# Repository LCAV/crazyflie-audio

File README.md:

# Audio processing for Crazyflie drone

This repository contains the hardware files, firmware and other documentation for the audio deck of the Crazyflie drone. 

## Overview

This repository is part of the experimental framework described in the [paper](https://doi.org/10.1109/LRA.2022.3194669):
```
F. Dümbgen, A. Hoffet, M. Kolundžija, A. Scholefield, and M. Vetterli, "Blind as a bat: audible 
echolocation on small robots", IEEE Robotics and Automation Letters (Early Access), 2022.
```

The framework includes all components listed below. The components are kept modular so that researchers may focus only on what's relevant to them. For instance, to recreate the audio extension deck and perform more research on audio-based navigation on drones, only repository 2. is necessary; to run the audio-based algorithms in ROS but for a different robot, only repository 1. is enough as a starting point.      

1. [ROS processing pipeline](https://github.com/LCAV/audioROS) for processing audio for tasks such as obstacle detection and sound source localization. 
2. [Audio deck firmware](https://github.com/LCAV/crazyflie-audio) (**this repository**), which also includes the PCB files for reproducing the audio deck. 
3. [Public datasets](https://github.com/LCAV/audio-localization-dataset), for audio-based localization on the e-puck2 robot and the Crazyflie drone. 
4. [Crazyflie firmware](https://github.com/LCAV/crazyflie-firmware) (fork from official vendor firmware), with an added [audio deck driver](https://github.com/LCAV/crazyflie-firmware/blob/master/src/deck/drivers/src/audio_deck.c).
5. [Gtsam extension](https://github.com/duembgen/gtsam) for performing factor-graph inference using the echolocation measurements. 

## Contents

- `firmware/`: Firmware to run on the audio shield, which extracts and transmits microphone data to the Crazyflie PCB. 
- `hardware/`: *KiCad* PCB design files for audio shield.
- `python/`: Helper functions to generate hard-coded sweeps etc. 
- `flight_control/`: Simple scripts to fly the Crazyflie drone for testing.
- `doc/`: Some documentation and helpers.

## Audio deck driver

The driver of the audio deck, running on the Crazyflie, is available in [this fork](https://github.com/lcav/crazyflie-firmware) of the official firmware.

## Contributors 

In alphabetical order:

- Isaac Bernardino Dinis 
- Frederike Dümbgen
- Adrien Hoffet

## License

All material in this repo is provided with the MIT license.

## EEPROM

Parameters to set in `crazyflie-lib-python/examples/write_ow.py`: 

```
mems[0].vid = 0xBC
mems[0].pid = 0xFF
board_name_id = OWElement.element_mapping[1]
board_rev_id = OWElement.element_mapping[2]
mems[0].elements[board_name_id] = 'Audio Shield'
mems[0].elements[board_rev_id] = 'V2'
```

## References

Please refer to the below publications for more information. 

[1] [RA-L paper](https://doi.org/10.1109/LRA.2022.3194669) (main reference)
```
F. Dümbgen, A. Hoffet, M. Kolundžija, A. Scholefield, and M. Vetterli, "Blind as a bat: audible 
echolocation on small robots", IEEE Robotics and Automation Letters (Early Access), 2022. 
```

[2] [Ph.D. dissertation](https://infoscience.epfl.ch/record/290057) (including additional methods and experimental analysis):  
```
F. Dümbgen, "Blind as a bat: spatial perception without sight", Ph.D. disseration, 
École Polytechnique Fédérale de Lausanne, 2021.
```

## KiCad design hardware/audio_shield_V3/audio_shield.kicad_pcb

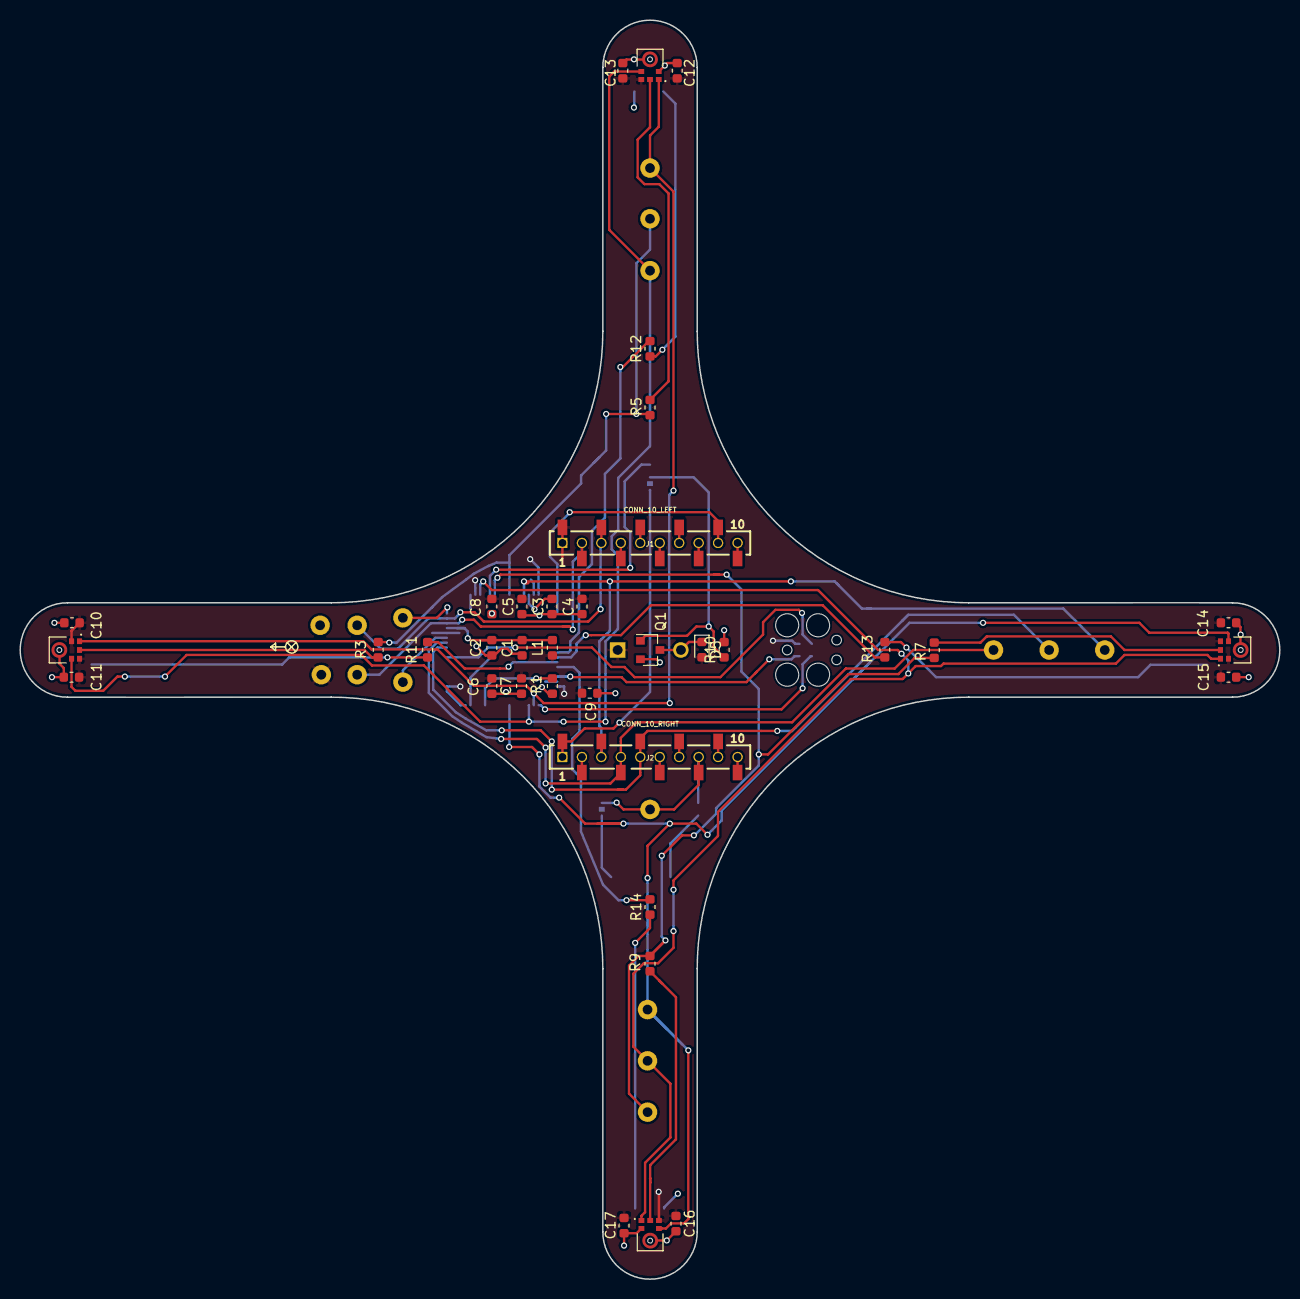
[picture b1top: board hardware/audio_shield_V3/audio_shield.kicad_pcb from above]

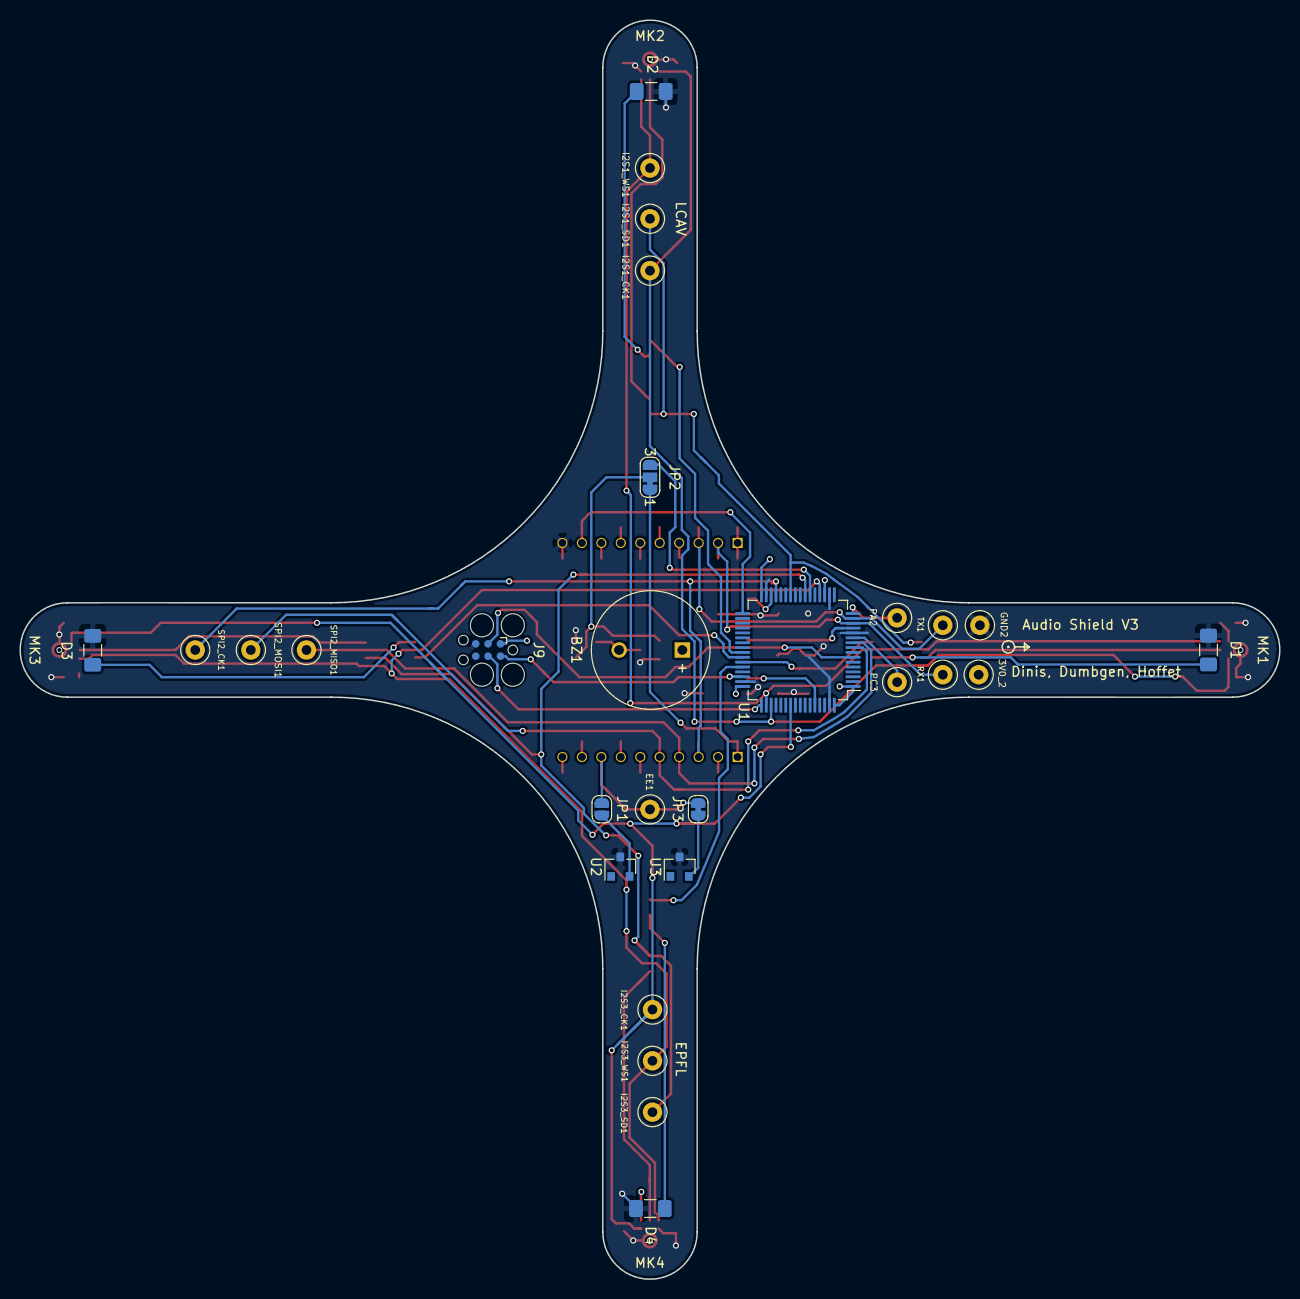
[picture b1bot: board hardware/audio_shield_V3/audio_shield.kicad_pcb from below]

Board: 2 copper layers, 129.5 x 129.4 mm, 64 parts (28 on the bottom side), 41 nets.

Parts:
3V0_2: TestPoint; TestPoint_Loop_D2.50mm_Drill1.0mm_LowProfile
BZ1: KXG1201B; MagneticBuzzer_ProSignal_ABT-410-RC
C1, C5, C6, C7, C8, C9, C11, C13, C15, C17: 100n; C_0603_1608Metric
C2: 1u; C_0603_1608Metric
C3, C4: 4.7u; C_0603_1608Metric
C10, C12, C14, C16: 220p; C_0603_1608Metric
D1: LED_G; R_1206_3216Metric_Pad1.42x1.75mm_HandSolder
D2, D3, D4: LED_R; R_1206_3216Metric_Pad1.42x1.75mm_HandSolder
D5: DIODE; D_0603_1608Metric
EE1: TestPoint; TestPoint_Loop_D2.50mm_Drill1.0mm_LowProfile
GND2: TestPoint; TestPoint_Loop_D2.50mm_Drill1.0mm_LowProfile
I2S1_CK1, I2S1_SD1, I2S1_WS1, I2S3_CK1, I2S3_SD1, I2S3_WS1: TestPoint; TestPoint_Loop_D2.50mm_Drill1.0mm_LowProfile
J1: CONN_10_LEFT; BF090-10-X-B2
J2: CONN_10_RIGHT; BF090-10-X-B2
J9: SWD_TC2030; Tag-Connect_TC2030-IDC-FP_2x03_P1.27mm_Vertical
JP1: Jumper_2_Open; SolderJumper-2_P1.3mm_Open_RoundedPad1.0x1.5mm
JP2: Jumper_3_Bridged12; SolderJumper-3_P1.3mm_Bridged12_RoundedPad1.0x1.5mm_NumberL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
JP3: Jumper_2_Bridged; SolderJumper-2_P1.3mm_Bridged_RoundedPad1.0x1.5mm
L1: 2.2uH/15mA; L_0603_1608Metric
MK1, MK2, MK3, MK4: SPH0645LM4H-B; MIC_SPH0645LM4H-B
PA2: TestPoint; TestPoint_Loop_D2.50mm_Drill1.0mm_LowProfile
PC3: TestPoint; TestPoint_Loop_D2.50mm_Drill1.0mm_LowProfile
Q1: BS170F; SOT-23
R1, R10: 10k; R_0603_1608Metric
R3, R5, R7, R9, R11, R12, R13, R14: 68; R_0603_1608Metric
RX1: TestPoint; TestPoint_Loop_D2.50mm_Drill1.0mm_LowProfile
SPI2_CK1, SPI2_MISO1, SPI2_MOSI1: TestPoint; TestPoint_Loop_D2.50mm_Drill1.0mm_LowProfile
TX1: TestPoint; TestPoint_Loop_D2.50mm_Drill1.0mm_LowProfile
U1: STM32F446RETx; LQFP-64_10x10mm_P0.5mm
U2, U3: DS2401Z; SOT-23

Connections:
+3V0: 3V0_2.1, BZ1.1, C4.1, C5.1, C6.1, C7.1, C8.1, C9.1, C10.2, C11.2, C12.2, C13.2, C14.2, C15.2, C16.2, C17.2, D5.2, J1.1, J9.1, L1.2, MK1.2, MK1.5, MK2.5, MK3.2, MK3.5, MK4.5, U1.1, U1.19, U1.32, U1.48, U1.64
/AD_Buzzer: JP2.3, U1.22
/CF_Buzzer: J2.1, JP2.1
/EEPROM: EE1.1, J2.8, JP1.1, JP3.1
/I2S1_CK: I2S3_CK1.1, MK3.4, MK4.4, U1.55
/I2S1_SD: I2S3_SD1.1, R7.2, R9.2, U1.23
/I2S1_WS: I2S3_WS1.1, MK3.1, MK4.1, U1.20
/I2S3_CK: I2S1_CK1.1, MK1.4, MK2.4, U1.51
/I2S3_SD: I2S1_SD1.1, R3.2, R5.2, U1.26
/I2S3_WS: I2S1_WS1.1, MK1.1, MK2.1, U1.50
/LED1: R12.2, U1.41
/LED2: R13.2, U1.42
/LED3: R11.2, U1.43
/LED4: R14.2, U1.44
/PA2: PA2.1, U1.16
/PC3: PC3.1, U1.11
/RX1: J1.2, RX1.1, U1.14
/SPI2_CK: J2.3, SPI2_CK1.1, U1.29
/SPI2_MISO: J2.4, SPI2_MISO1.1, U1.10
/SPI2_MOSI: J2.5, SPI2_MOSI1.1, U1.9
/SPI2_NSS: J1.9, U1.33
/SWCLK: J9.4, U1.49
/SWDIO: J9.2, U1.46
/TX1: J1.3, TX1.1, U1.15
/nRESET: J9.3, U1.7
GND: C1.2, C2.2, C3.2, C4.2, C5.2, C6.2, C7.2, C8.2, C9.2, C10.1, C11.1, C12.1, C13.1, C14.1, C15.1, C16.1, C17.1, D1.1, D2.1, D3.1, D4.1, GND2.1, J1.10, J9.5, MK1.3, MK2.2, MK2.3, MK3.3, MK4.2, MK4.3, Q1.2, R1.2, R10.2, U1.12, U1.18, U1.31, U1.47, U1.63, U2.3, U3.3
unnamed: BZ1.2, D5.1, Q1.3
unnamed: C1.1, C2.1, L1.1, U1.13
unnamed: C3.1, U1.30
unnamed: D1.2, R11.1
unnamed: D2.2, R12.1
unnamed: D3.2, R13.1
unnamed: D4.2, R14.1
unnamed: JP1.2, U2.2
unnamed: JP2.2, Q1.1, R10.1
unnamed: JP3.2, U3.2
unnamed: MK1.6, R3.1
unnamed: MK2.6, R5.1
unnamed: MK3.6, R7.1
unnamed: MK4.6, R9.1
unnamed: R1.1, U1.60

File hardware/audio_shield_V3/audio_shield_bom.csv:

"Source:","/Users/hoffet/Documents/LCAV_Repo/audioROS/crazyflie-audio/hardware/audio_shield_V3/audio_shield.sch"
"Date:","2021 March 11, Thursday 16:21:59"
"Tool:","Eeschema (5.1.6-0-10_14)"
"Generator:","/private/var/folders/_0/5tv0ncr12mg82wg0rc7s58xw0000gp/T/AppTranslocation/677E2EFB-6496-4B17-BDC3-31EE06410C6D/d/kicad.app/Contents/SharedSupport/plugins/bom_csv_grouped_by_value_with_fp.py"
"Component Count:","64"
"Ref","Qnty","Value","Cmp name","Footprint","Description","Vendor"
"3V0_2, EE1, GND2, I2S1_CK1, I2S1_SD1, I2S1_WS1, I2S3_CK1, I2S3_SD1, I2S3_WS1, PA2, PC3, RX1, SPI2_CK1, SPI2_MISO1, SPI2_MOSI1, TX1, ","16","TestPoint","TestPoint","audio_shield:TestPoint_Loop_D2.50mm_Drill1.0mm_LowProfile","test point",""
"BZ1, ","1","KXG1201B","Buzzer","Buzzer_Beeper:MagneticBuzzer_ProSignal_ABT-410-RC","Buzzer, polarized",""
"C1, C5, C6, C7, C8, C9, C11, C13, C15, C17, ","10","100n","C","Capacitor_SMD:C_0603_1608Metric","Unpolarized capacitor",""
"C2, ","1","1u","C","Capacitor_SMD:C_0603_1608Metric","Unpolarized capacitor",""
"C3, C4, ","2","4.7u","C","Capacitor_SMD:C_0603_1608Metric","Unpolarized capacitor",""
"C10, C12, C14, C16, ","4","220p","C","Capacitor_SMD:C_0603_1608Metric","Unpolarized capacitor",""
"D1, ","1","LED_G","LED","Resistor_SMD:R_1206_3216Metric_Pad1.42x1.75mm_HandSolder","Light emitting diode",""
"D2, D3, D4, ","3","LED_R","LED","Resistor_SMD:R_1206_3216Metric_Pad1.42x1.75mm_HandSolder","Light emitting diode",""
"J1, ","1","CONN_10_LEFT","Conn_01x10","audio_shield:BF090-10-X-B1","Generic connector, single row, 01x10, script generated (kicad-library-utils/schlib/autogen/connector/)",""
"J2, ","1","CONN_10_RIGHT","Conn_01x10","audio_shield:BF090-10-X-B1","Generic connector, single row, 01x10, script generated (kicad-library-utils/schlib/autogen/connector/)",""
"J9, ","1","SWD_TC2030","SWD_TC2030","Connector:Tag-Connect_TC2030-IDC-FP_2x03_P1.27mm_Vertical","",""
"J48, ","1","STLINK-V3MINI Placeholder","AVR-JTAG-10","","Atmel 10-pin JTAG connector",""
"JP1, ","1","Jumper_2_Open","Jumper_2_Open","Jumper:SolderJumper-2_P1.3mm_Open_RoundedPad1.0x1.5mm","Jumper, 2-pole, open",""
"JP2, ","1","Jumper_3_Bridged12","Jumper_3_Bridged12","Jumper:SolderJumper-3_P1.3mm_Bridged12_RoundedPad1.0x1.5mm_NumberLabels","Jumper, 3-pole, pins 1+2 closed/bridged",""
"JP3, ","1","Jumper_2_Bridged","Jumper_2_Bridged","Jumper:SolderJumper-2_P1.3mm_Bridged_RoundedPad1.0x1.5mm","Jumper, 2-pole, closed/bridged",""
"L1, ","1","2.2uH/15mA","L","Inductor_SMD:L_0603_1608Metric","Inductor",""
"MK1, MK2, MK3, MK4, ","4","SPH0645LM4H-B","SPH0645LM4H-B","audio_shield:MIC_SPH0645LM4H-B","",""
"Q1, ","1","BS170F","BS170F","Package_TO_SOT_SMD:SOT-23","0.15A Id, 60V Vds, N-Channel MOSFET, SOT-23",""
"R1, R10, ","2","10k","R","Resistor_SMD:R_0603_1608Metric","Resistor",""
"R3, R5, R7, R9, R11, R12, R13, R14, ","8","68","R","Resistor_SMD:R_0603_1608Metric","Resistor",""
"U1, ","1","STM32F446RETx","STM32F446RETx","Package_QFP:LQFP-64_10x10mm_P0.5mm","ARM Cortex-M4 MCU, 512KB flash, 128KB RAM, 180MHz, 1.8-3.6V, 50 GPIO, LQFP-64",""
"U2, U3, ","2","DS28E05R+T","DS28E05P","Package_SO_J-Lead:TSOC-6_3.76x3.94mm_P1.27mm","",""

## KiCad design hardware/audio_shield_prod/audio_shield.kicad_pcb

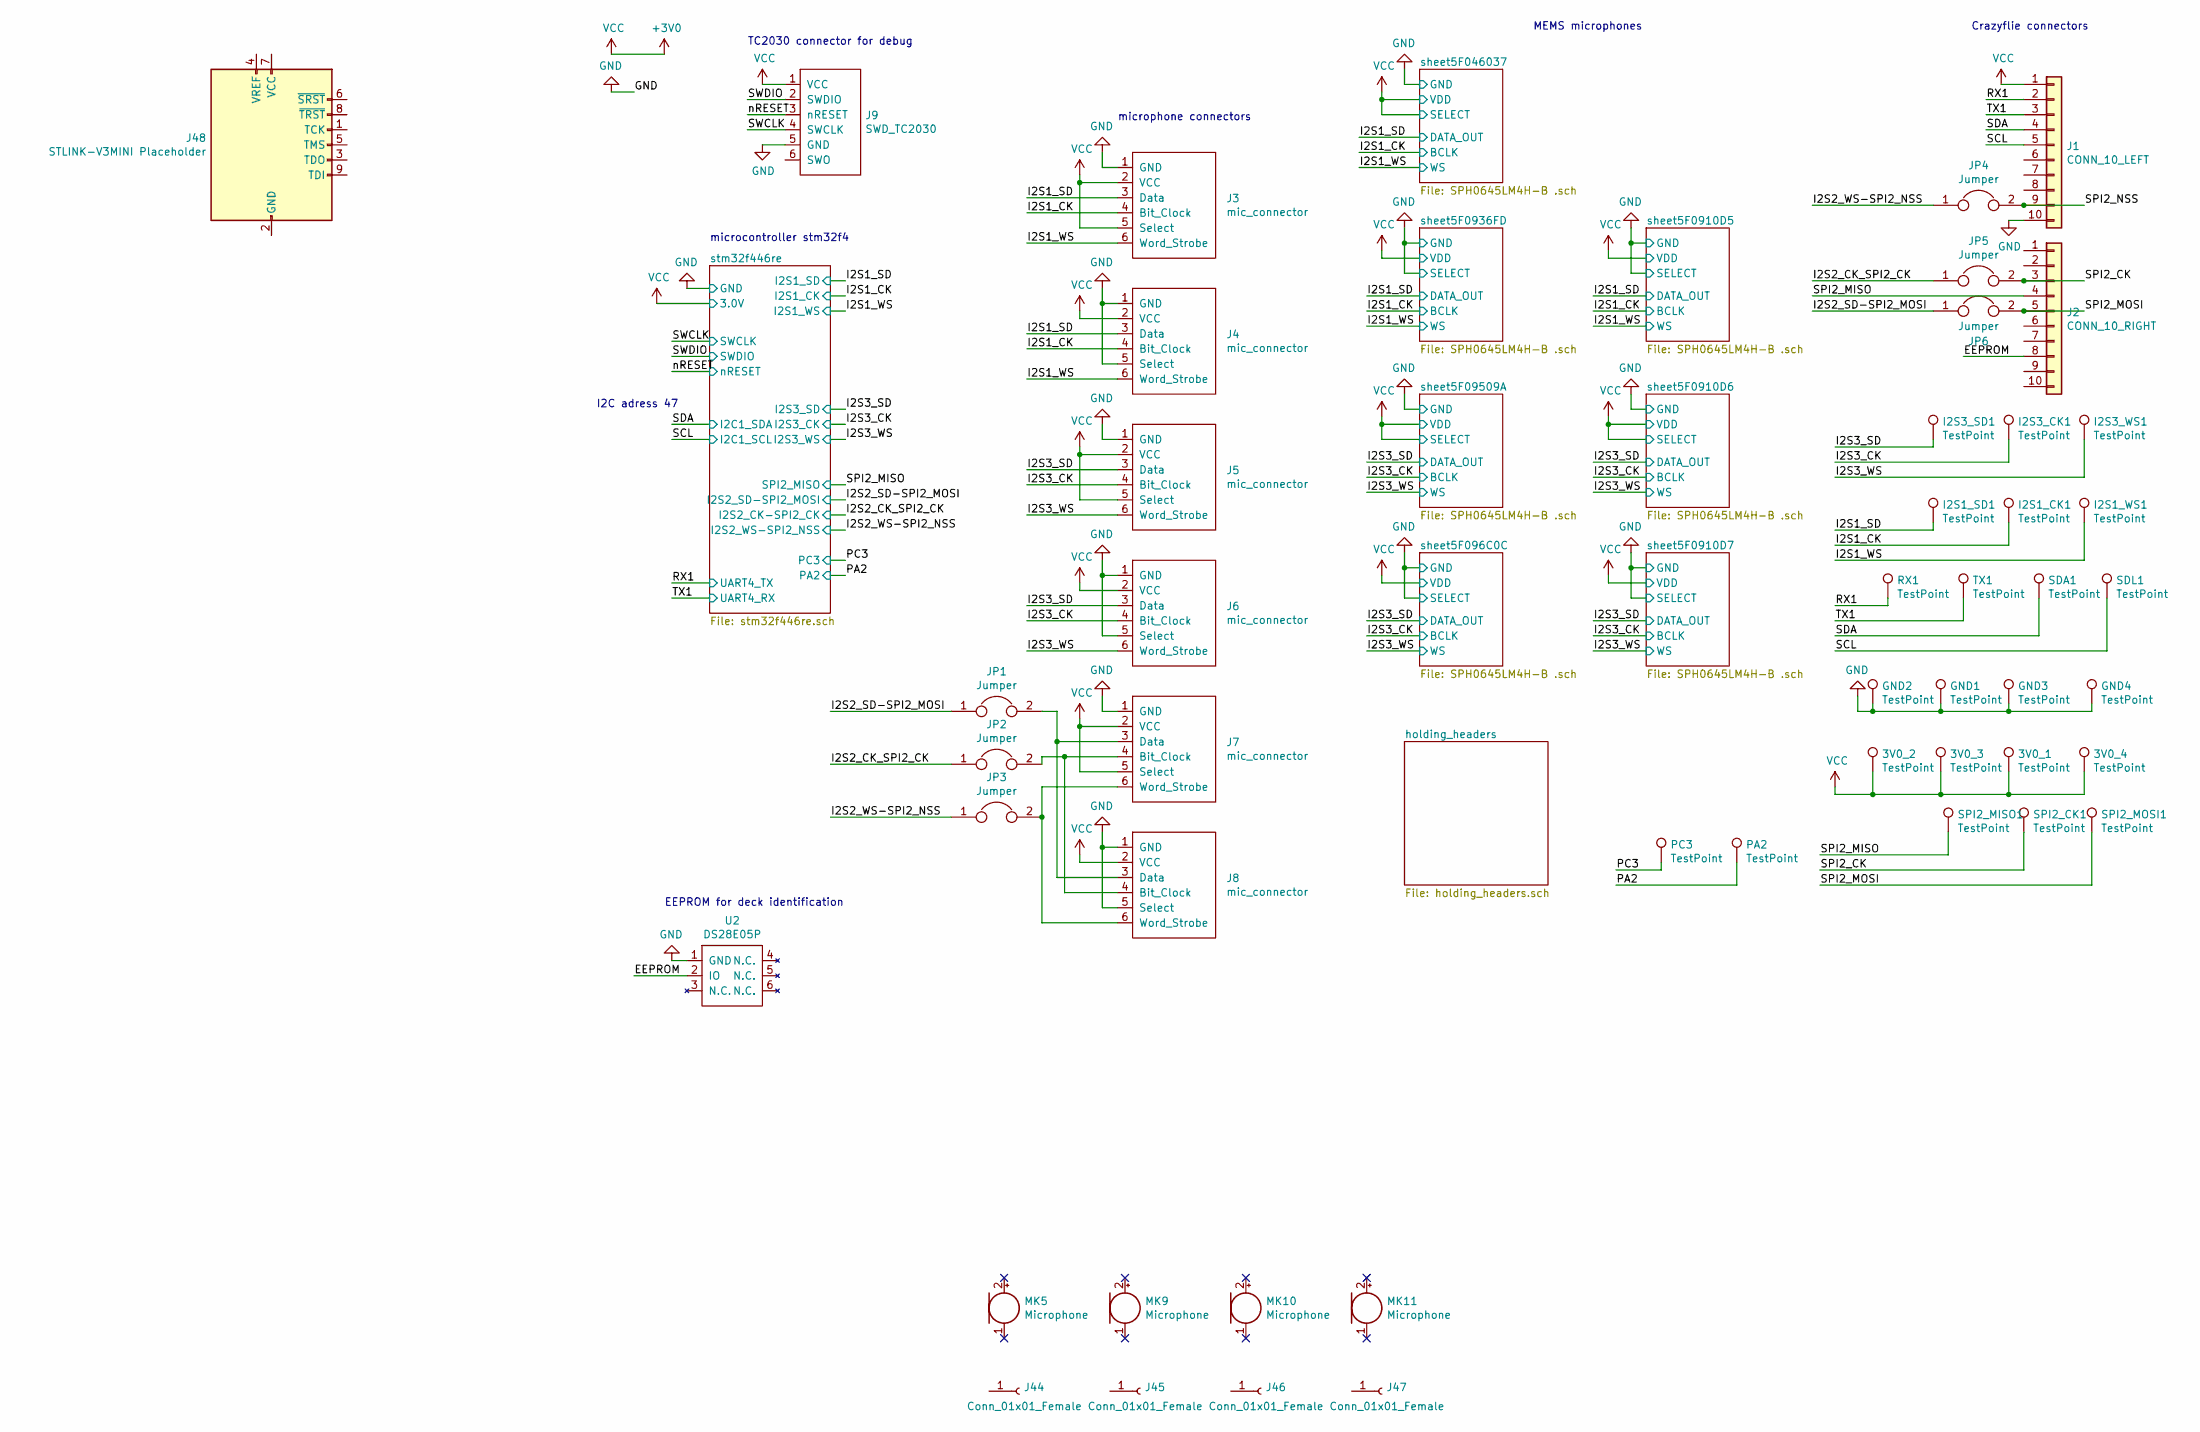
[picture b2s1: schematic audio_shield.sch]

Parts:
3V0_1, 3V0_2, 3V0_3, 3V0_4: TestPoint; TestPoint_Loop_D2.50mm_Drill1.0mm_LowProfile
GND1, GND2, GND3, GND4: TestPoint; TestPoint_Loop_D2.50mm_Drill1.0mm_LowProfile
I2S1_CK1, I2S1_SD1, I2S1_WS1, I2S3_CK1, I2S3_SD1, I2S3_WS1: TestPoint; TestPoint_Loop_D2.50mm_Drill1.0mm_LowProfile
J1: CONN_10_LEFT; BF090-10-X-B1
J2: CONN_10_RIGHT; BF090-10-X-B1
J3, J4, J5, J6, J7, J8: mic_connector; 6288_series_8_pos
J9: SWD_TC2030; Tag-Connect_TC2030-IDC-FP_2x03_P1.27mm_Vertical
J44, J45, J46, J47: Conn_01x01_Female
J48: STLINK-V3MINI Placeholder
JP1, JP2, JP3: Jumper; SolderJumper-2_P1.3mm_Bridged_Pad1.0x1.5mm
JP4, JP5, JP6: Jumper; SolderJumper-2_P1.3mm_Open_Pad1.0x1.5mm
MK5, MK9, MK10, MK11: Microphone
PA2: TestPoint; TestPoint_Loop_D2.50mm_Drill1.0mm_LowProfile
PC3: TestPoint; TestPoint_Loop_D2.50mm_Drill1.0mm_LowProfile
RX1: TestPoint; TestPoint_Loop_D2.50mm_Drill1.0mm_LowProfile
SDA1: TestPoint; TestPoint_Loop_D2.50mm_Drill1.0mm_LowProfile
SDL1: TestPoint; TestPoint_Loop_D2.50mm_Drill1.0mm_LowProfile
SPI2_CK1, SPI2_MISO1, SPI2_MOSI1: TestPoint; TestPoint_Loop_D2.50mm_Drill1.0mm_LowProfile
TX1: TestPoint; TestPoint_Loop_D2.50mm_Drill1.0mm_LowProfile
U2: DS28E05P; TSOC-6_3.76x3.94mm_P1.27mm

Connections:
+3V0: 3V0_1.1, 3V0_2.1, 3V0_3.1, 3V0_4.1, J1.1, J3.2 (VCC), J3.5 (Select), J4.2 (VCC), J5.2 (VCC), J5.5 (Select), J6.2 (VCC), J7.2 (VCC), J7.5 (Select), J8.2 (VCC), J9.1 (VCC); also elsewhere on the board
/EEPROM: J2.8, U2.2 (IO)
/I2S1_CK: I2S1_CK1.1, J3.4 (Bit_Clock), J4.4 (Bit_Clock); also elsewhere on the board
/I2S1_SD: I2S1_SD1.1, J3.3 (Data), J4.3 (Data); also elsewhere on the board
/I2S1_WS: I2S1_WS1.1, J3.6 (Word_Strobe), J4.6 (Word_Strobe); also elsewhere on the board
/I2S2_CK_SPI2_CK: JP2.1, JP5.1; also elsewhere on the board
/I2S2_SD-SPI2_MOSI: JP1.1, JP6.1; also elsewhere on the board
/I2S2_WS-SPI2_NSS: JP3.1, JP4.1; also elsewhere on the board
/I2S3_CK: I2S3_CK1.1, J5.4 (Bit_Clock), J6.4 (Bit_Clock); also elsewhere on the board
/I2S3_SD: I2S3_SD1.1, J5.3 (Data), J6.3 (Data); also elsewhere on the board
/I2S3_WS: I2S3_WS1.1, J5.6 (Word_Strobe), J6.6 (Word_Strobe); also elsewhere on the board
/PA2: PA2.1; also elsewhere on the board
/PC3: PC3.1; also elsewhere on the board
/RX1: J1.2, RX1.1; also elsewhere on the board
/SCL: J1.5, SDL1.1; also elsewhere on the board
/SDA: J1.4, SDA1.1; also elsewhere on the board
/SPI2_CK: J2.3, JP5.2, SPI2_CK1.1
/SPI2_MISO: J2.4, SPI2_MISO1.1; also elsewhere on the board
/SPI2_MOSI: J2.5, JP6.2, SPI2_MOSI1.1
/SPI2_NSS: J1.9, JP4.2
/SWCLK: J9.4 (SWCLK); also elsewhere on the board
/SWDIO: J9.2 (SWDIO); also elsewhere on the board
/TX1: J1.3, TX1.1; also elsewhere on the board
/nRESET: J9.3 (nRESET); also elsewhere on the board
GND: GND1.1, GND2.1, GND3.1, GND4.1, J1.10, J3.1 (GND), J4.1 (GND), J4.5 (Select), J5.1 (GND), J6.1 (GND), J6.5 (Select), J7.1 (GND), J8.1 (GND), J8.5 (Select), J9.5 (GND), U2.1 (GND); also elsewhere on the board
unnamed: J7.3 (Data), J8.3 (Data), JP1.2
unnamed: J7.4 (Bit_Clock), J8.4 (Bit_Clock), JP2.2
unnamed: J7.6 (Word_Strobe), J8.6 (Word_Strobe), JP3.2
unnamed: J48.2 (GND), J48.10 (GND)

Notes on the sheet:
microcontroller stm32f4
microphone connectors
TC2030 connector for debug
MEMS microphones
Crazyflie connectors
EEPROM for deck identification
I2C adress 47

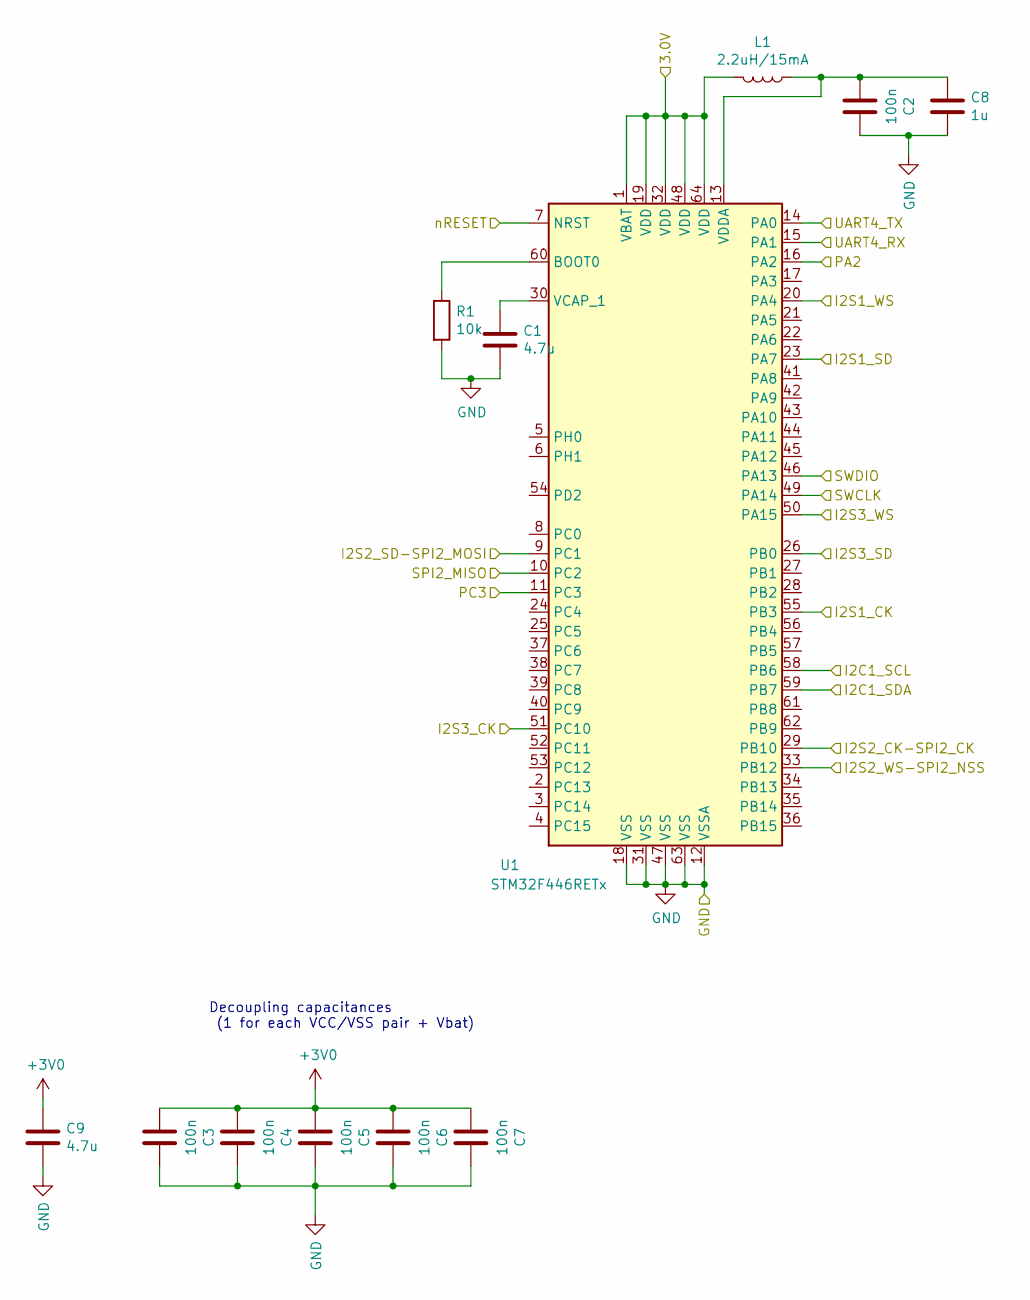
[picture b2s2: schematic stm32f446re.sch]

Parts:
C1, C9: 4.7u; C_0603_1608Metric
C2, C3, C4, C5, C6, C7: 100n; C_0603_1608Metric
C8: 1u; C_0603_1608Metric
L1: 2.2uH/15mA; L_0603_1608Metric
R1: 10k; R_0603_1608Metric
U1: STM32F446RETx; LQFP-64_10x10mm_P0.5mm

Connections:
+3V0: C3.1, C4.1, C5.1, C6.1, C7.1, C9.1, L1.2, U1.1 (VBAT), U1.19 (VDD), U1.32 (VDD), U1.48 (VDD), U1.64 (VDD); also elsewhere on the board
/I2S1_CK: U1.55 (PB3); also elsewhere on the board
/I2S1_SD: U1.23 (PA7); also elsewhere on the board
/I2S1_WS: U1.20 (PA4); also elsewhere on the board
/I2S2_CK_SPI2_CK: U1.29 (PB10); also elsewhere on the board
/I2S2_SD-SPI2_MOSI: U1.9 (PC1); also elsewhere on the board
/I2S2_WS-SPI2_NSS: U1.33 (PB12); also elsewhere on the board
/I2S3_CK: U1.51 (PC10); also elsewhere on the board
/I2S3_SD: U1.26 (PB0); also elsewhere on the board
/I2S3_WS: U1.50 (PA15); also elsewhere on the board
/PA2: U1.16 (PA2); also elsewhere on the board
/PC3: U1.11 (PC3); also elsewhere on the board
/RX1: U1.14 (PA0); also elsewhere on the board
/SCL: U1.58 (PB6); also elsewhere on the board
/SDA: U1.59 (PB7); also elsewhere on the board
/SPI2_MISO: U1.10 (PC2); also elsewhere on the board
/SWCLK: U1.49 (PA14); also elsewhere on the board
/SWDIO: U1.46 (PA13); also elsewhere on the board
/TX1: U1.15 (PA1); also elsewhere on the board
/nRESET: U1.7 (NRST); also elsewhere on the board
GND: C1.2, C2.2, C3.2, C4.2, C5.2, C6.2, C7.2, C8.2, C9.2, R1.2, U1.12 (VSSA), U1.18 (VSS), U1.31 (VSS), U1.47 (VSS), U1.63 (VSS); also elsewhere on the board
unnamed: C1.1, U1.30 (VCAP_1)
unnamed: C2.1, C8.1, L1.1, U1.13 (VDDA)
unnamed: R1.1, U1.60 (BOOT0)

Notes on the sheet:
Decoupling capacitances (1 for each VCC/VSS pair + Vbat)

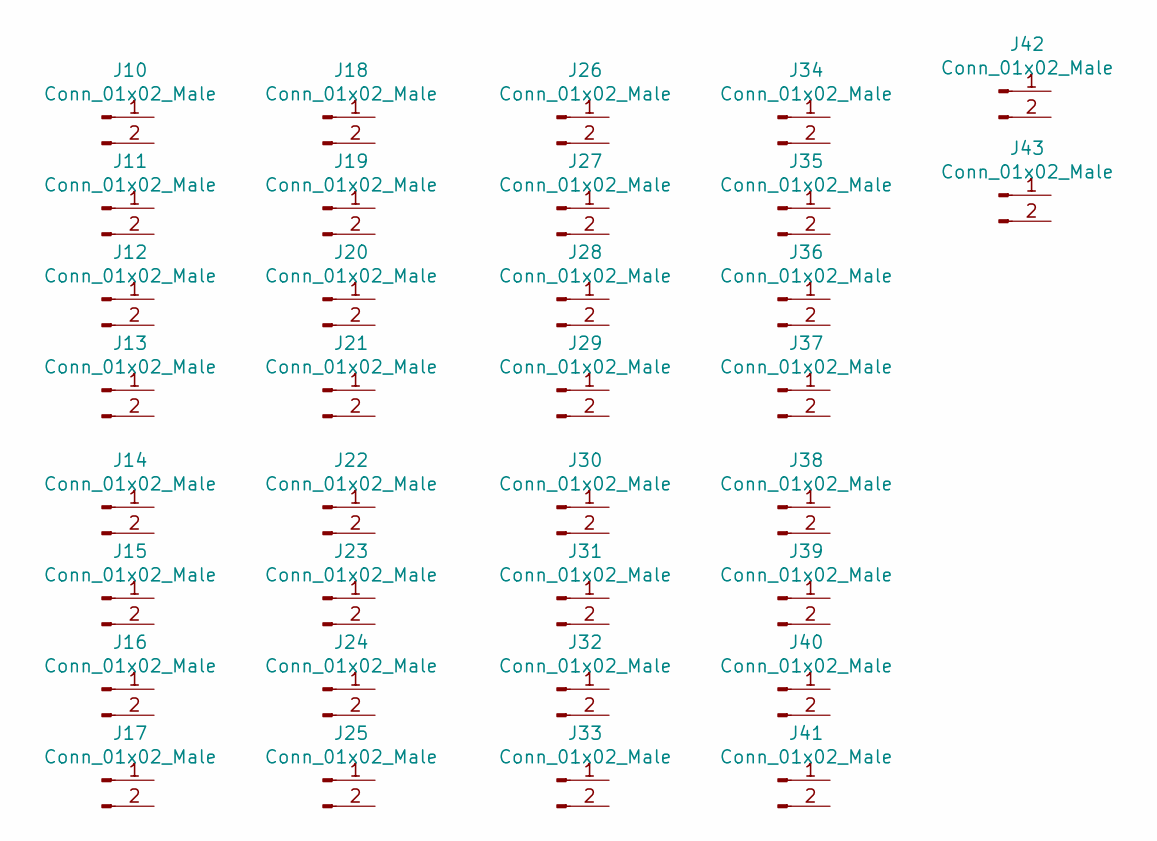
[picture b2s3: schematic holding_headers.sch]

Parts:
J10, J11, J12, J13, J14, J15, J16, J17, J18, J19, J20, J21, J22, J23, J24, J25, J26, J27, J28, J29, J30, J31, J32, J33, J34, J35, J36, J37, J38, J39, J40, J41, J42, J43: Conn_01x02_Male; PinHeader_1x02_P1.00mm_Vertical_SMD_Pin1Left

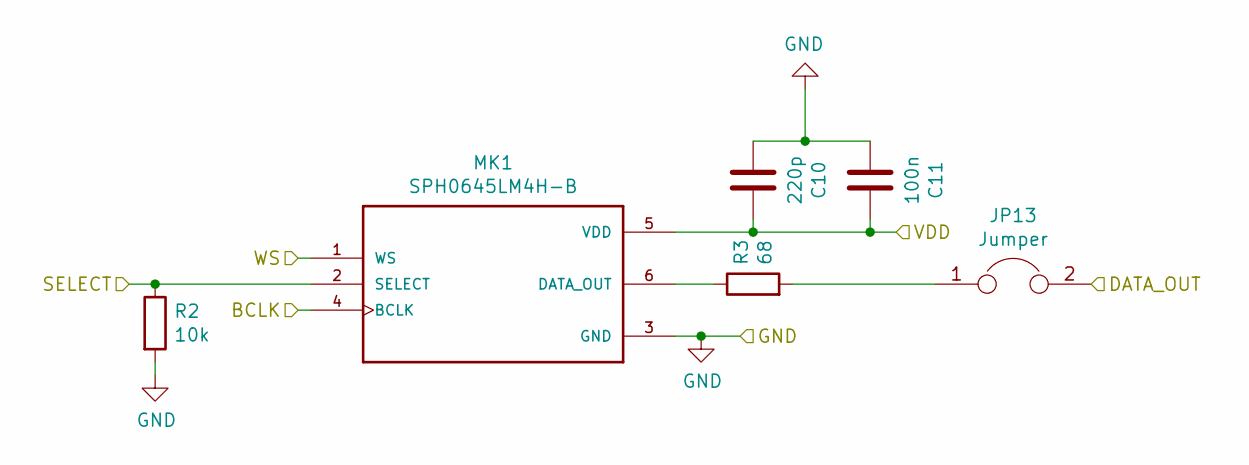
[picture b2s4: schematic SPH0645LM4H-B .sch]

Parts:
C10: 100n; C_0603_1608Metric
C11: 220p; C_0603_1608Metric
JP12: Jumper; SolderJumper-2_P1.3mm_Bridged_Pad1.0x1.5mm
MK1: SPH0645LM4H-B; MIC_SPH0645LM4H-B
R2: 10k; R_0603_1608Metric
R3: 68; R_0603_1608Metric

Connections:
+3V0: C10.2, C11.2, MK1.2 (SELECT), MK1.5 (VDD), R2.1; also elsewhere on the board
/I2S1_CK: MK1.4 (BCLK); also elsewhere on the board
/I2S1_SD: JP12.2; also elsewhere on the board
/I2S1_WS: MK1.1 (WS); also elsewhere on the board
GND: C10.1, C11.1, MK1.3 (GND), R2.2; also elsewhere on the board
unnamed: MK1.6 (DATA_OUT), R3.1

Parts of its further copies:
C12, C14, C16, C18, C20, C22, C24: 220p; C_0603_1608Metric
C13, C15, C17, C19, C21, C23, C25: 100n; C_0603_1608Metric
JP7, JP8, JP9, JP10, JP11, JP13: Jumper; SolderJumper-2_P1.3mm_Bridged_Pad1.0x1.5mm
MK2, MK3, MK4, MK6, MK7, MK8: SPH0645LM4H-B; MIC_SPH0645LM4H-B
R4, R6, R8, R10, R12, R14, R16: 10k; R_0603_1608Metric
R5, R7, R9, R11, R13, R15, R17: 68; R_0603_1608Metric

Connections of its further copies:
+3V0: C12.2, C13.2, C14.2, C15.2, C16.2, C17.2, C20.2, C21.2, C22.2, C23.2, C24.2, C25.2, MK2.5 (VDD), MK3.2 (SELECT), MK3.5 (VDD), MK4.5 (VDD), MK6.5 (VDD), MK7.2 (SELECT), MK7.5 (VDD), MK8.5 (VDD), R6.1, R14.1; also elsewhere on the board
/I2S1_CK: MK2.4 (BCLK), MK6.4 (BCLK); also elsewhere on the board
/I2S1_SD: JP7.2, JP13.2; also elsewhere on the board
/I2S1_WS: MK2.1 (WS), MK6.1 (WS); also elsewhere on the board
/I2S3_CK: MK3.4 (BCLK), MK4.4 (BCLK), MK7.4 (BCLK), MK8.4 (BCLK); also elsewhere on the board
/I2S3_SD: JP8.2, JP9.2, JP10.2, JP11.2; also elsewhere on the board
/I2S3_WS: MK3.1 (WS), MK4.1 (WS), MK7.1 (WS), MK8.1 (WS); also elsewhere on the board
GND: C12.1, C13.1, C14.1, C15.1, C16.1, C17.1, C20.1, C21.1, C22.1, C23.1, C24.1, C25.1, MK2.2 (SELECT), MK2.3 (GND), MK3.3 (GND), MK4.2 (SELECT), MK4.3 (GND), MK6.2 (SELECT), MK6.3 (GND), MK7.3 (GND), MK8.2 (SELECT), MK8.3 (GND), R4.1, R4.2, R6.2, R8.1, R8.2, R12.1, R12.2, R14.2, R16.1, R16.2; also elsewhere on the board
unnamed: JP7.1, R13.2
unnamed: JP8.1, R15.2
unnamed: JP9.1, R17.2
unnamed: JP10.1, R9.2
unnamed: JP11.1, R7.2
unnamed: MK2.6 (DATA_OUT), R5.1
unnamed: MK3.6 (DATA_OUT), R7.1
unnamed: MK4.6 (DATA_OUT), R9.1
unnamed: MK6.6 (DATA_OUT), R13.1
unnamed: MK7.6 (DATA_OUT), R15.1
unnamed: MK8.6 (DATA_OUT), R17.1

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

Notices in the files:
hardware/audio_shield_V3/audio_shield.kicad_pcb:
Licensed under CC-BY 4.0
